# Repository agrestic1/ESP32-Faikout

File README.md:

## Support

You can support this project in many ways, including testing and diagnostics, merge requests, clearly described issues and suggestions, and [buying Faikout boards from us](https://shop.revk.uk?mrlHiG1i) (shipped worldwide). Thank you all for your support. This is open source so others can make and sell (with trademark restrictions). AI based bug reports or MRs will get you blocked.

# ESP32-Faikout

Everyone knows Daikin make some of the best air conditioners out there, mechanically speaking. Sadly their WiFi control modules are not so good, especially the latest models which are all cloud based, require an internet connection to even work, and are slow.

This code/module provides local control via web interface, MQTT, and HomeAssistant integration, all with no cloud crap.

* There is also a new [Faikout Remote Control](https://remote.revk.uk/) available, BLE linked to the Faikout, with environmental sensors, available now.

I'd like to thank the contributors, but contributions are made and accepted on basis that you issue your contribution under the same GPL licence as the project. Forks are allowed on the basis that your forks are on the same GPL licence as the project.

## Trademark

This is an open source project, but bear in mind you cannot sell boards bearing the Andrews & Arnold Ltd name, the A&A logo, the registered trademark Faikout, the registered trademark AJK logo, or the GS1 allocated EANs assigned to Andrews & Arnold Ltd.

Note the name change from Faikin to Faikout as Daikin complained to Amazon and caused a lot of issues. As such Faikout is now a registered trademark to avoid such issues.

## Home Assistant Integration

There has been a lot of work on integrating with Home Assistant as a climate device, and other sensors. This is all based on using MQTT (either HA mosquitto broker, or a broker to which HA also connects). This provides real time responses and sensor data and works very well.

In addition, for other management systems than HA, the *legacy* Daikin local HTTP URLs are also supported to some extent. The support coverage is not as good, and maintence of this is less of a priority - but as always (human) suggestions and pull requests are welcome in this area. If you are using the old Daikin HA integration which uses these legacy HTTP URLs, please update to using MQTT. The config is automatic over MQTT - you just have to set the broken, username, and password. 

## Further manuals / links

- [Work in progress](https://codeberg.org/RevK/ESP32-Faikout/wiki/Work-in-progress)
- [Wiring](https://codeberg.org/RevK/ESP32-Faikout/wiki/Wiring)
- [Setup](Manuals/Setup.md) Manual
- [Controls](Manuals/Controls.md) Manual
- [Advanced](Manuals/Advanced.md) Manual
- [ESP8266 port](https://github.com/Sonic-Amiga/ESP8266-Faikin) of this code
- [list of supported air-con](https://codeberg.org/RevK/ESP32-Faikout/wiki/List-of-confirmed-working-air-con-units) WiKi (please update as needed)
- [DoC](Manuals/DoC.md) and Vulnerability disclosure policy
- [S21](Manuals/S21.md) reverse engineered details of `S21` protocol

For support, see issues.

## Safety

Always propely isolate power before opening your air-con. Take care as dangerous voltages. Some connector types have dangerous voltage in operation.

### Ethernet (and WiFi)

The Ethernet board has an RJ45 10/100 Ethernet connector for improved reliability and privacy. The Ethernet has an isolating transformer and clearances, but I have to stress **this is a prototype/dev board for specialist/hobbyist use only, and is NOT certified for grid power safety isolation. DO NOT USE WITH X403 CONNECTOR or any connector with dangerous voltages.**

### PoE Ethernet (and WiFi)

The PoE Ethernet board has an RJ45 10/100 Ethernet connector for improved reliability and privacy, with PoE power for the Faikout module. The PoE power module has electrical isolation. The board also has opto isolators for the S21 connection, electrically isolating it from the air conditioning unit. This adds extra layers of safety, however I have to stress **this is a prototype/dev board for specialist/hobbyist use only, and is NOT certified for grid power safety isolation.**

*Note that Ethernet uses more power - there are some Daikin models with much less power from the air-con, for these PoE may be a better choice for Ethernet use, as the main board (and Ethernet chip) is powered from the PoE, and not the air-con.*

## PCB and case

Buy from [shop.revk.uk](https://shop.revk.uk?mrlHiG1i). Also available from a third party in Australia eBay.

New Ethernet option.

New Opto-isiolated PoE Ethernet option.

Board are supplied in a panel, with snap off parts. The basic Faikout board can be two sizes 45x36mm or 40x16mm.

## Why I made this

The history is that, after years of using Daikin air-con in my old home, and using the local http control, in my new house in Wales the WiFi was all cloud based with no local control, and useless, and slow. Just configuring it was a nightmare. I spent all day reverse engineering it and making a new module to provide local control. Pull requests and feature ideas welcome.

This whole project is almost entirely by me, but with some valuable contributions from others (thank you). All of my bits are copyright by me and Andrews & Arnold Ltd who sponsor the whole project, and released under GPL. Whilst not required by the licence, attribution and links would be appreciated if you reuse this.

## How to get one

But also, the PCB designs are published, including production files for [JLCPCB](https://jlcpcb.com). You need to remove trademarks, etc, and you would also need something to program them (TC2030 lead). Obviously you need some experience with PCB ordering and diagnostics if getting your own boards made.

# Set-up

Appears as access point with simple web page to set up on local WiFI. On iPhone the setup page auto-loads.

# Operation

Local interactive web control page using *hostname*.local, no app required, no external internet required.

- [Setup](Manuals/Setup.md) Manual
- [Controls](Manuals/Controls.md) Manual
- [Advanced](Manuals/Advanced.md) Manual

# Design

* KiCad PCB designs included, with JLCPCB production files
* 3D printed case STL files
* Documentation of reverse engineered protocol included

Basically, Daikin have gone all cloudy with the latest WiFi controllers. This module is designed to provide an alternative.

* Simple local web based control with live websocket status, easy to save as desktop icon on a mobile phone
* MQTT reporting and controls
* Works with Home Assistant over MQTT - note Home Assistant can work with HomeKit
* Includes linux mysql/mariadb based logging and graphing tools
* Works with [EnvMon](https://codeberg.org/RevK/ESP32-EnvMon) Environmental Monitor for finer control and status display
* or, works with BlueCoinT and Telink [BLE temperature sensor](Manuals/BLE.md) as a remote reference in an auto mode
* Automatically works out if S21 or X50 protocol (used on bigger/ducted units)
* Backwards compatible direct `/aircon/...` URLs

# Building code yourself

Git clone this `--recursive` to get all the submodules, and it should build with just `make`. There are make targets for other variations, but this hardware is the `make pico` or `make s3` version. The `make` actually runs the normal `idf.py` to build which then uses cmake. `make menuconfig` can be used to fine tune the settings, but the defaults should be mostly sane. `make flash` should work to program. If flashing yourself, you will need a programming lead, e.g. [Tazmotizer](https://codeberg.org/RevK/Tasmotizer-PCB) or similar, and of course the full ESP IDF environment. The latest boards also have 4 pads for direct USB connection to flash with no adaptor. The modules on Amazon come pre-loaded and can upgrade over the air.

The code is normally set up to automatically upgrade the software, checking roughly once a week. You can change this in settings via MQTT.

If you build yourself, you either need no code signing, or your own signing key. This will break auto-updates which try to load my code releases, so you need to adjuist settings `otahost` and `otaauto` accordingly. You can set these in the build config, along with WiFi settings, etc.

## Flashing code

You will need to connect a suitable programming lead. Boards have a tag-connect compatible header for a [TC2030-USB-NL](https://www.tag-connect.com/product/tc2030-usb-nl) lead. Note that the latest boards have test pads on the back which include USB, so you can solder a USB lead if necessary.

See [https://codeberg.org/RevK/ESP32-RevK](https://codeberg.org/RevK/ESP32-RevK) for more details of how to flash the files easily.

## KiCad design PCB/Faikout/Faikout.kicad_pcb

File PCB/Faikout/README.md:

# Faikout

## Trademark

This project is subject to the licence in the LICENCE file, and even if that says it is an open source project, you cannot sell boards or cases bearing the Andrews & Arnold Ltd name, the A&A logo, the registered trademark AJK logo, or other registered trademarks, or any GS1 allocated EANs/barcode assigned to Andrews & Arnold Ltd.

## PCB Designs

These files are for use with [KiCAD](https://www.kicad.org).

- [Faikout](Faikout.kicad_pro)

## 3D

3D case designs are normally automatically created from the PCB so as to ensure correct details and placement of apertures, etc.

|Design|Bottom|Top|Combined|
|------|------|---|--------|
|Faikout||||

## PCB Images Faikout

---

*Auto generated README.md 2026-11-19T10:28:16*

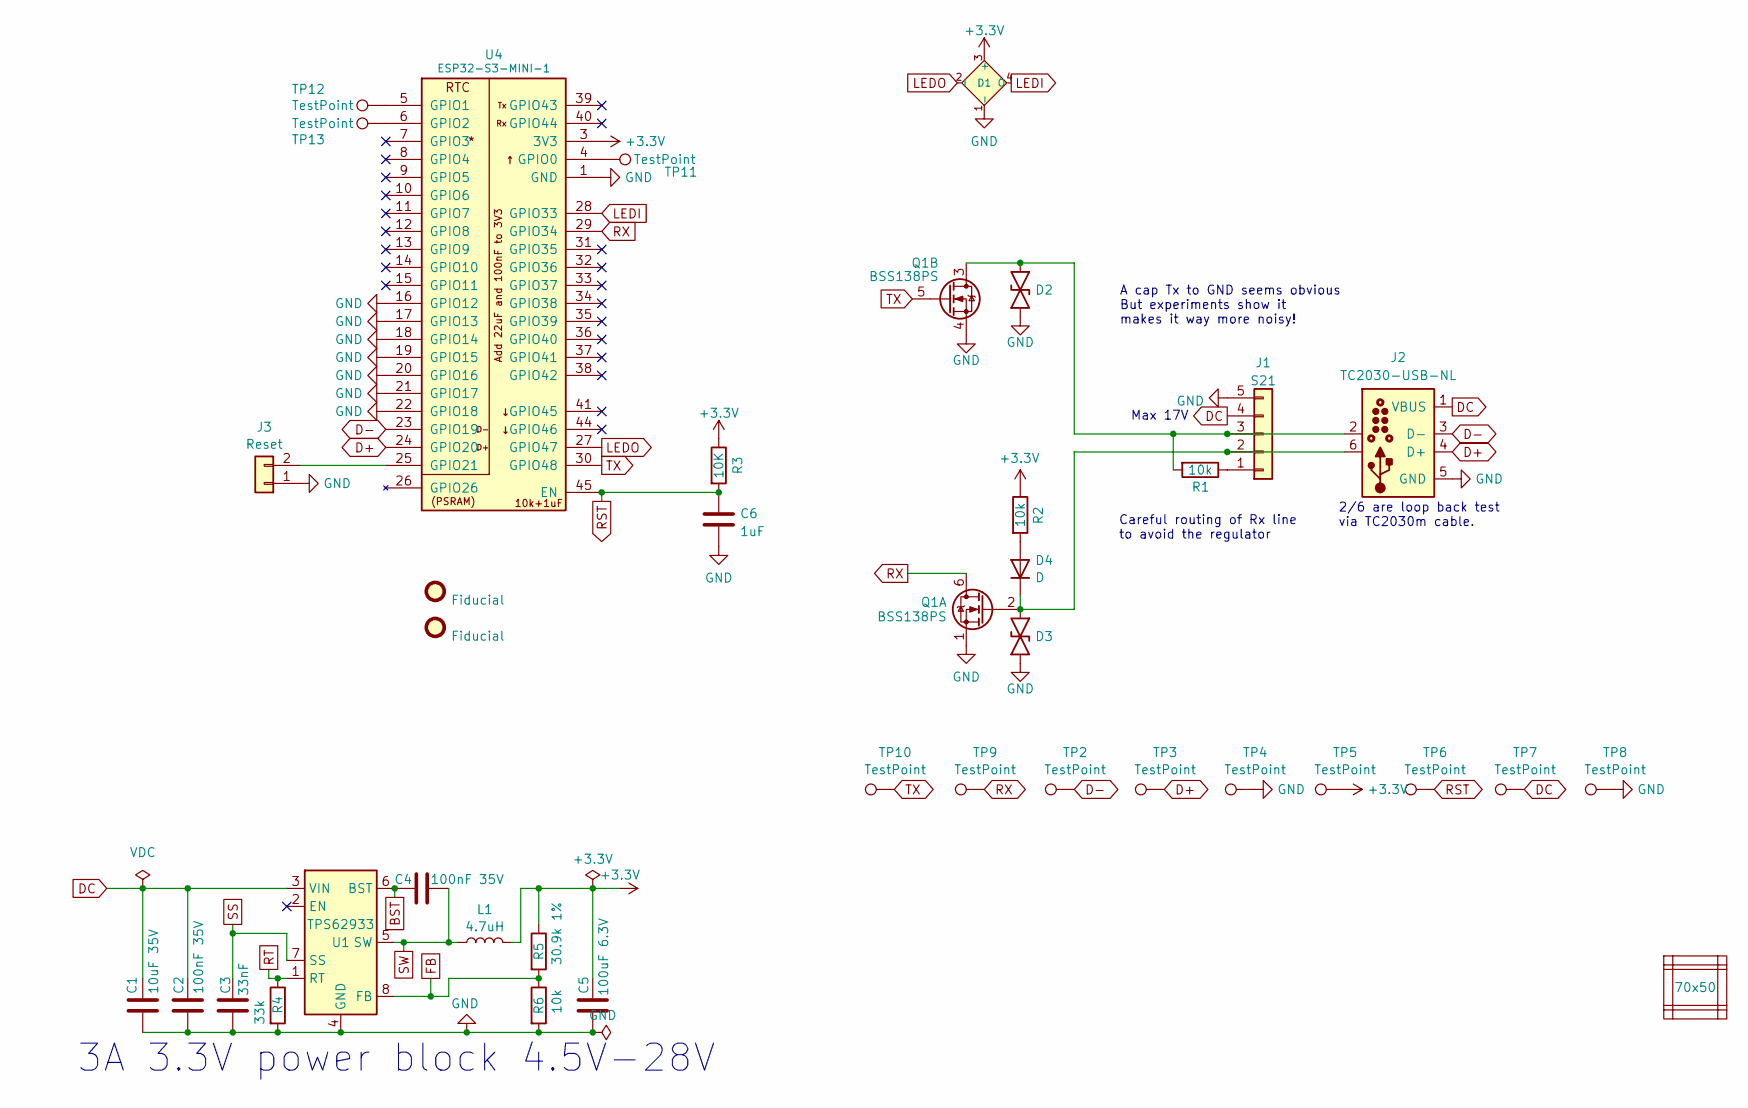
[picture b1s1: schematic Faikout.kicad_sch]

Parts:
C1: 10uF 35V; C_0603; MPN C22367827
C2, C4: 100nF 35V; C_0201; MPN C181043
C3: 33nF; C_0201; MPN C5142554
C5: 100uF 6.3V; C_0805; MPN C141660
C6: 1uF; C_0201
D1: XL-1615RGBC-2812B; SMD1615; MPN C5349954
D2, D3: DFN1006-2L; MPN C5137770
D4: D; D_0402; MPN C28642302
FID2, FID3: Fiducial; Fiducial_1mm_Mask2mm
J1: S21; JST_EH_S5B-EH_1x05_P2.50mm_Horizontal; MPN C265103
J2: TC2030-USB-NL; Tag-Connect_TC2030-IDC-NL_2x03_P1.27mm_Vertical
J3: Reset; AA-Pad
L1: 4.7uH; L_6x6; MPN C32684
PCB1: 70x50; PCB7050
Q1: BSS138PS; SOT-363_SC-70-6; MPN C5224289
R1, R2, R6: 10k; R_0201; MPN C106225
R3: 10K; R_0201; MPN C106225
R4: 33k; R_0201; MPN C473534
R5: 30.9k 1%; R_0201; MPN C473585
TP2, TP3, TP4, TP5, TP6, TP7, TP8, TP9, TP10, TP11, TP12, TP13: TestPoint; PAD-2mm
U1: TPS62933; SOT-583-8; MPN C3200405
U4: ESP32-S3-MINI-1; MPN C3013941
V1, V2, V3, V4: VCUT70N
V5, V6: VCUT50N

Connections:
+3.3V: C5.1, D1.3 (+), L1.2, R2.1, R3.1, R5.1, TP5.1 (1_1), U4.3 (3V3)
BST: C4.1, U1.6 (BST)
D+: J2.4 (D+), TP3.1 (1_1), U4.24 (GPIO20)
D-: J2.3 (D-), TP2.1 (1_1), U4.23 (GPIO19)
DC: C1.1, C2.1, J1.4, J2.1 (VBUS), TP7.1 (1_1), U1.3 (VIN)
FB: R5.2, R6.1, U1.8 (FB)
GND: C1.2, C2.2, C3.2, C5.2, C6.2, D1.1 (-), D2.1, D3.1, J1.5, J2.5 (GND), J3.1, Q1.1 (SN), Q1.4 (DP), R4.2, R6.2, TP4.1 (1_1), TP8.1 (1_1), U1.4 (GND), U4.1 (GND), U4.2 (GND), U4.16 (GPIO12), U4.17 (GPIO13), U4.18 (GPIO14), U4.19 (GPIO15), U4.20 (GPIO16), U4.21 (GPIO17), U4.22 (GPIO18), U4.42 (GND), U4.43 (GND), U4.46 (GND), U4.47 (GND), U4.48 (GND), U4.49 (GND), U4.50 (GND), U4.51 (GND), U4.52 (GND), U4.53 (GND), U4.54 (GND), U4.55 (GND), U4.56 (GND), U4.57 (GND), U4.58 (GND), U4.59 (GND), U4.60 (GND), U4.61 (GND), U4.62 (GND), U4.63 (GND), U4.64 (GND), U4.65 (GND)
LEDI: D1.4 (O), U4.28 (GPIO33)
LEDO: D1.2 (I), U4.27 (GPIO47)
unnamed: D4.2 (A), R2.2
unnamed: D3.2, D4.1 (K), J1.2, J2.6, Q1.2 (GN)
unnamed: J1.1, R1.1
unnamed: D2.2, J1.3, J2.2, Q1.3 (SP), R1.2
unnamed: J3.2, U4.25 (GPIO21)
unnamed: TP11.1 (1_1), U4.4 (GPIO0)
unnamed: TP12.1 (1_1), U4.5 (GPIO1)
unnamed: TP13.1 (1_1), U4.6 (GPIO2)
RST: C6.1, R3.2, TP6.1 (1_1), U4.45 (EN)
RT: R4.1, U1.1 (RT)
RX: Q1.6 (DN), TP9.1 (1_1), U4.29 (GPIO34)
SS: C3.1, U1.7 (SS)
SW: C4.2, L1.1, U1.5 (SW)
TX: Q1.5 (GP), TP10.1 (1_1), U4.30 (GPIO48)

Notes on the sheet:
Careful routing of Rx line to avoid the regulator
3A 3.3V power block 4.5V-28V
Max 17V
2/6 are loop back test via TC2030m cable.
A cap Tx to GND seems obvious But experiments show it makes it way more noisy!

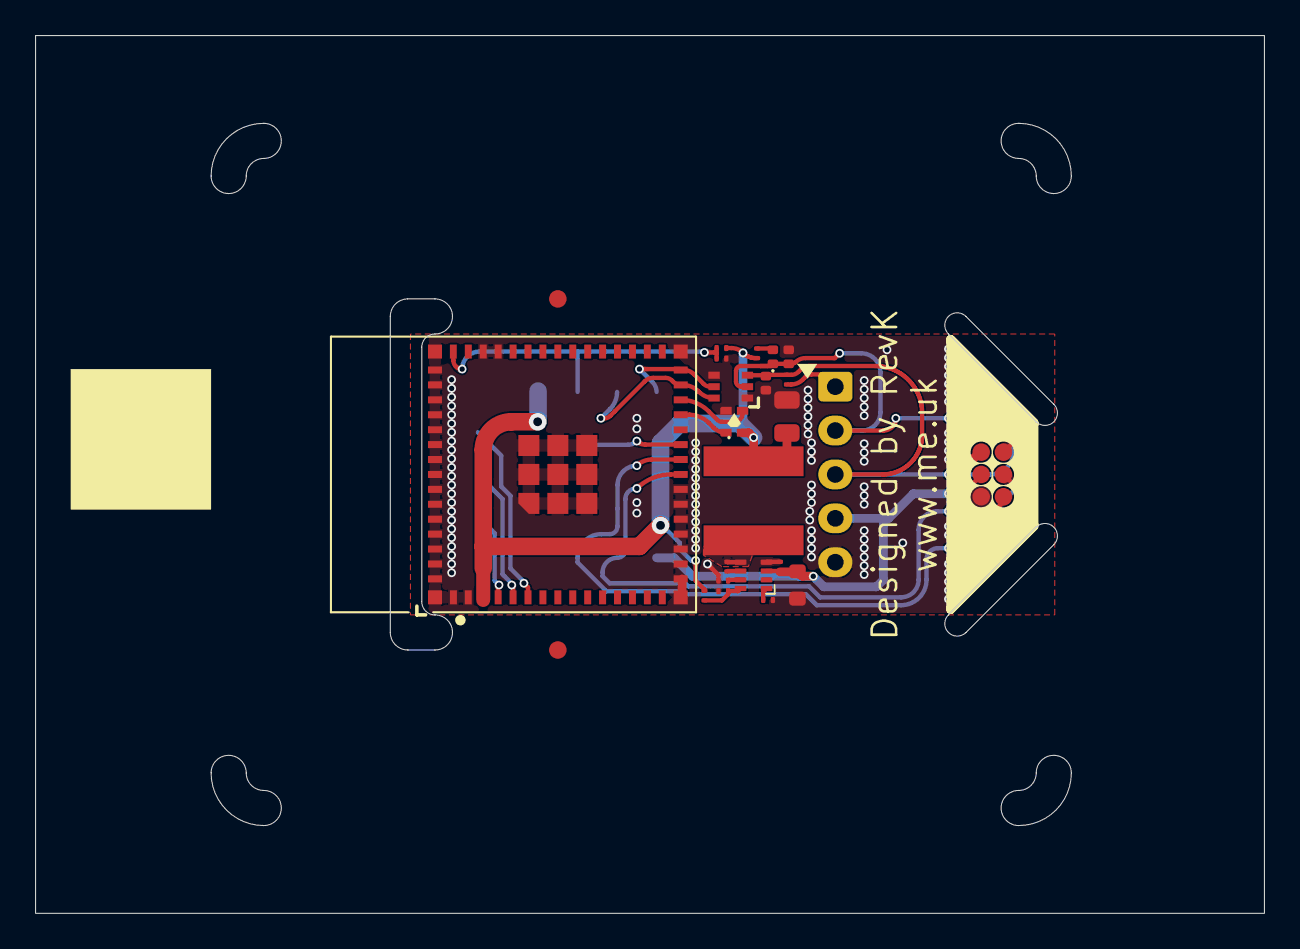
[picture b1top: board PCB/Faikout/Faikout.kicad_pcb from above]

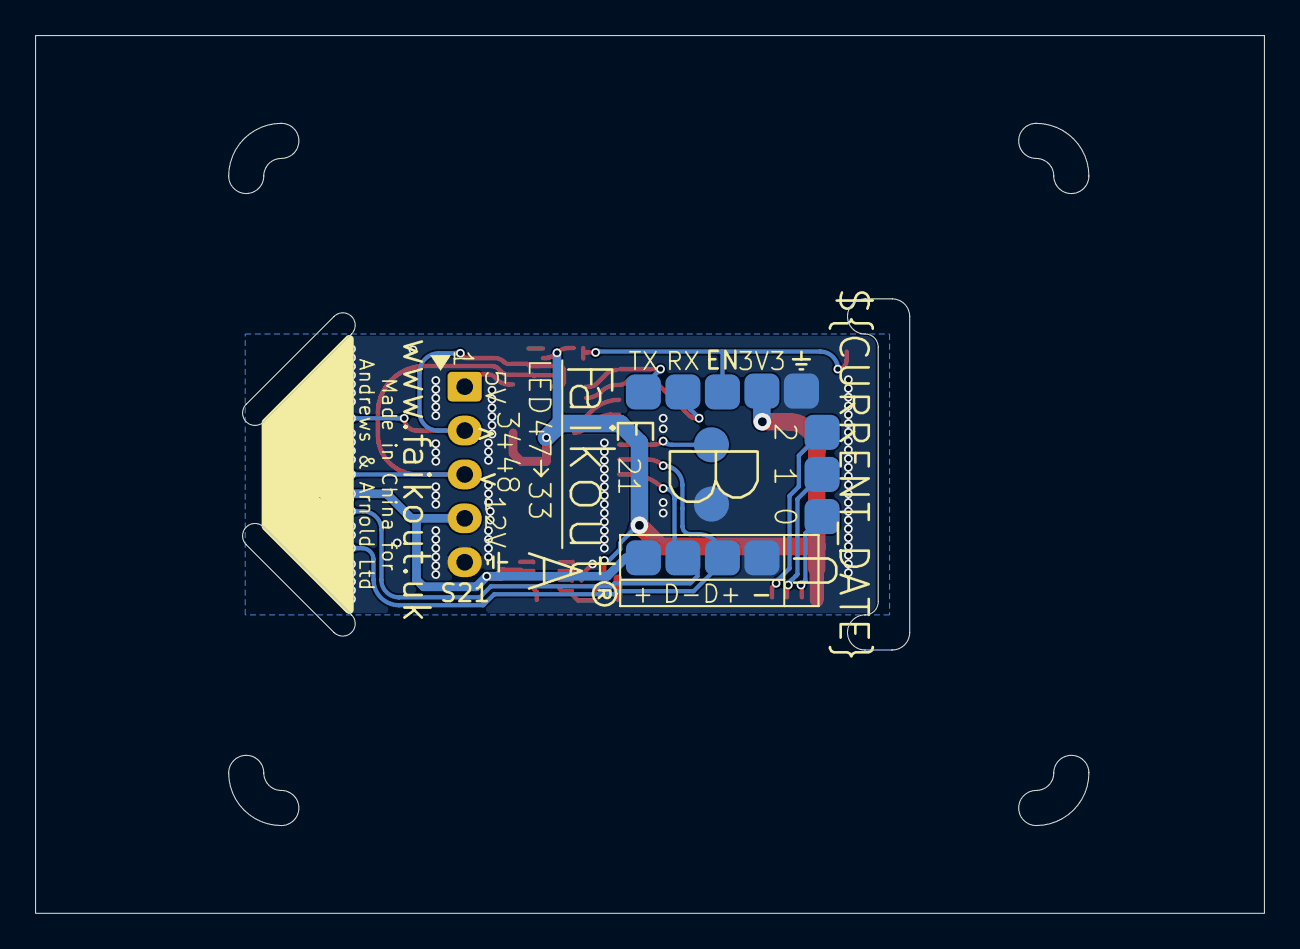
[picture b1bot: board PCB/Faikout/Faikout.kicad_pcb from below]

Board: 2 copper layers, 70.0 x 50.0 mm, 44 parts (15 on the bottom side), 23 nets.

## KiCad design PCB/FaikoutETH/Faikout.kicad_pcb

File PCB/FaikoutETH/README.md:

# FaikoutETH

## Trademark

This project is subject to the licence in the LICENCE file, and even if that says it is an open source project, you cannot sell boards or cases bearing the Andrews & Arnold Ltd name, the A&A logo, the registered trademark AJK logo, or other registered trademarks, or any GS1 allocated EANs/barcode assigned to Andrews & Arnold Ltd.

## PCB Designs

These files are for use with [KiCAD](https://www.kicad.org).

- [Faikout](Faikout.kicad_pro)

## 3D

3D case designs are normally automatically created from the PCB so as to ensure correct details and placement of apertures, etc.

|Design|Bottom|Top|Combined|
|------|------|---|--------|
|Faikout||||

## PCB Images Faikout

---

*Auto generated README.md 2026-11-19T10:28:18*

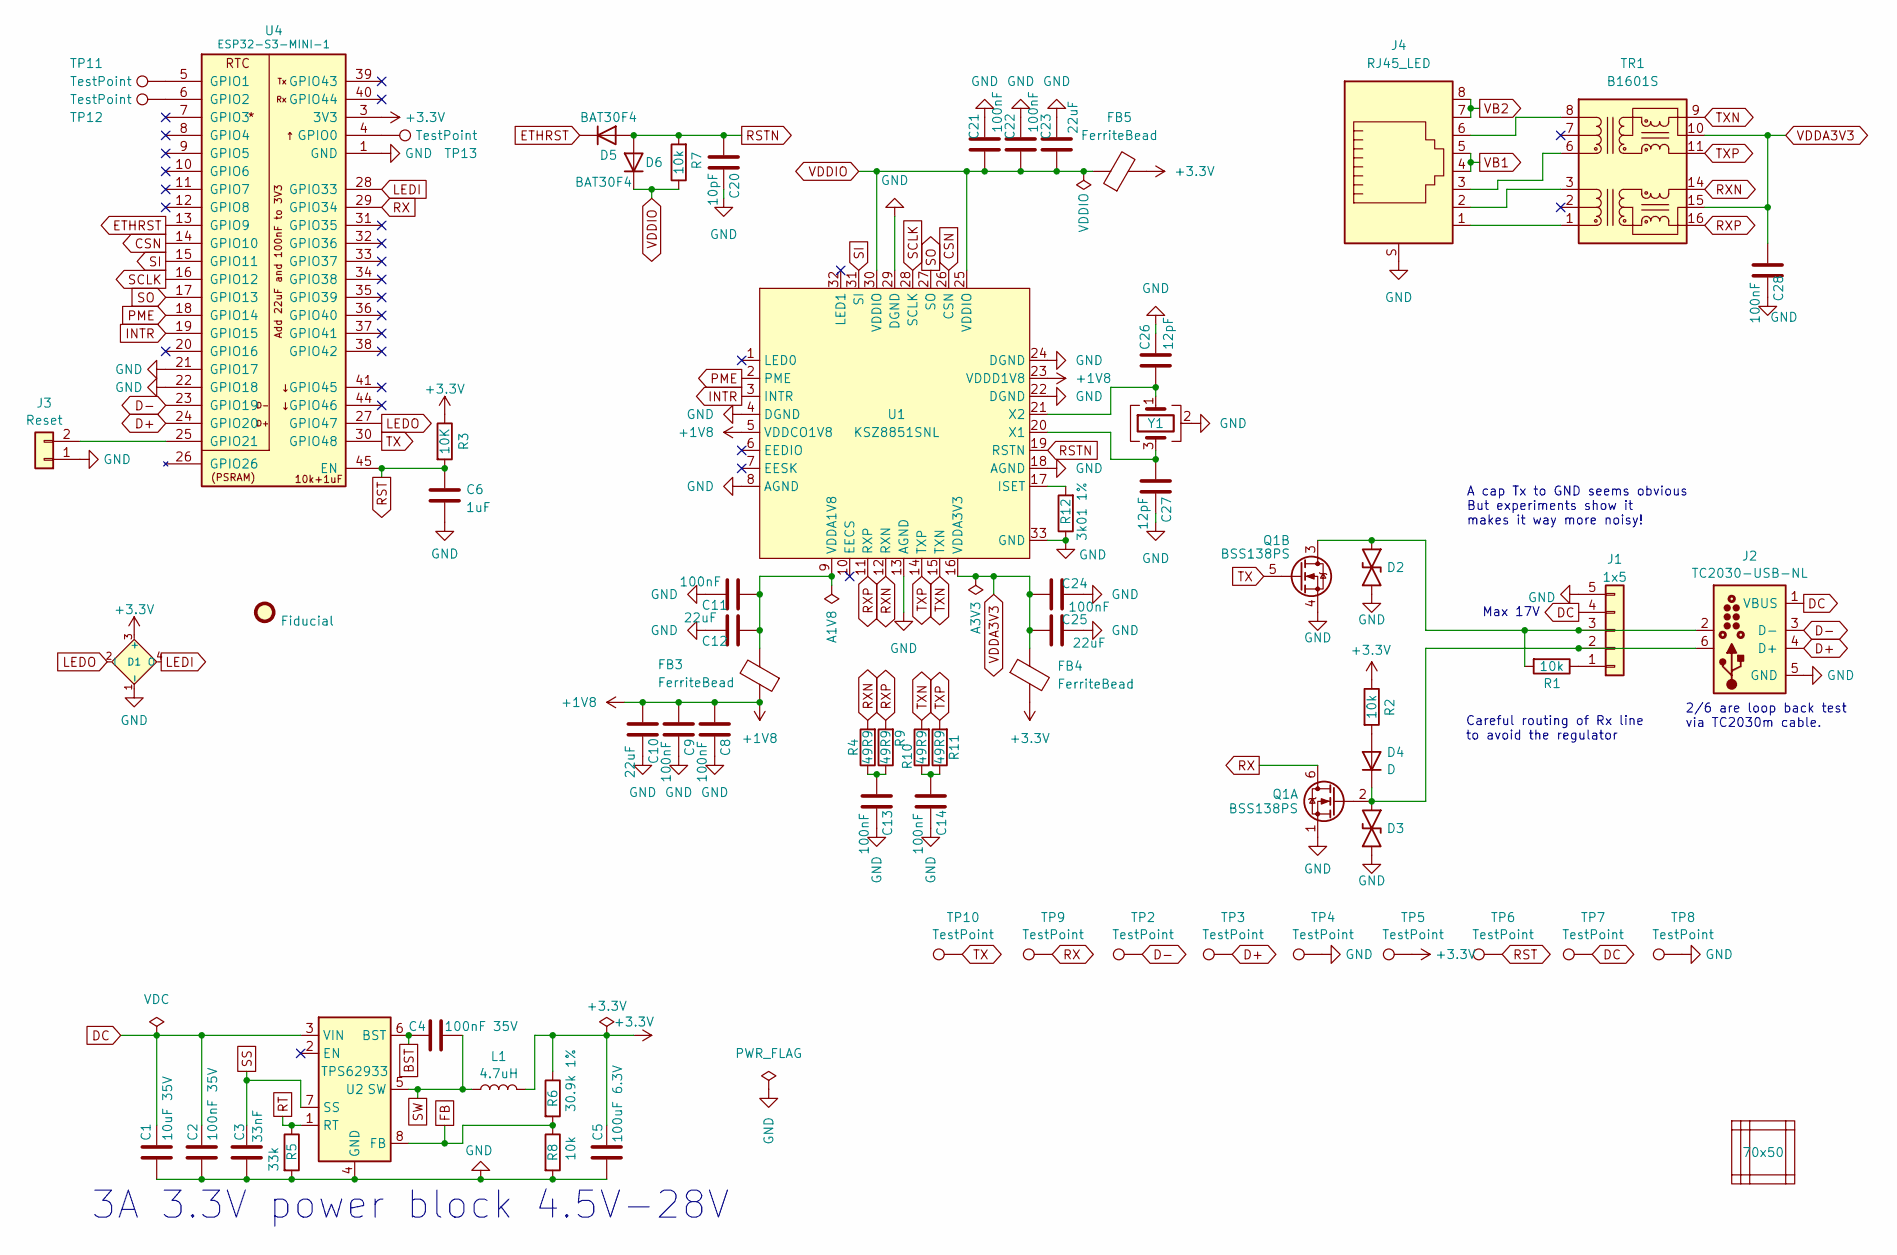
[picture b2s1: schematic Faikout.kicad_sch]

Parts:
C1: 10uF 35V; C_0603; MPN C22367827
C2, C4: 100nF 35V; C_0201; MPN C181043
C3: 33nF; C_0201; MPN C5142554
C5: 100uF 6.3V; C_0805; MPN C141660
C6: 1uF; C_0201; MPN C87143
C8, C9, C11, C13, C14, C21, C22, C24, C28: 100nF; C_0201; MPN C66938
C10, C12, C23, C25: 22uF; C_0402; MPN C105226
C20: 10pF; C_0201; MPN C76921
C26, C27: 12pF; C_0201
D1: XL-1615RGBC-2812B; SMD1615; MPN C5349954
D2, D3: DFN1006-2L; MPN C5137770
D4: D; D_0402; MPN C28642302
D5, D6: BAT30F4; D_0201; MPN C18197832
FB3, FB4, FB5: FerriteBead; L_0603; MPN C14709
FID2: Fiducial; Fiducial_1mm_Mask2mm
J1: 1x5; JST_EH_S5B-EH_1x05_P2.50mm_Horizontal; MPN C265103
J2: TC2030-USB-NL; Tag-Connect_TC2030-IDC-NL_2x03_P1.27mm_Vertical
J3: Reset; AA-Pad
J4: RJ45_LED; RC01516; MPN C708636
L1: 4.7uH; L_6x6; MPN C32684
PCB1: 70x50; PCB7050
Q1: BSS138PS; SOT-363_SC-70-6; MPN C193381
R1, R2, R7: 10k; R_0201; MPN C138117
R3: 10K; R_0201; MPN C138117
R4, R9, R10, R11: 49R9; R_0201; MPN C100141
R5: 33k; R_0201; MPN C473534
R6: 30.9k 1%; R_0201; MPN C473585
R8: 10k; R_0201; MPN C106225
R12: 3k01 1%; R_0201; MPN C320817
TP2, TP3, TP4, TP5, TP6, TP7, TP8, TP9, TP10, TP11, TP12, TP13: TestPoint; PAD-2mm
TR1: B1601S; MPN C510548
U1: KSZ8851SNL; QFN-32-1EP_5x5mm_P0.5mm_EP3.7x3.7mm-hot; MPN C633272
U2: TPS62933; SOT-583-8; MPN C3200405
U4: ESP32-S3-MINI-1; MPN C3013941
V3, V4: VCUT70N
V5, V6, V7: VCUT50N
Y1: Crystal_GND24; Crystal-3.2x2.5; MPN C5155480

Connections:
+1V8: C8.1, C9.1, C10.1, FB3.1, U1.5 (VDDCO1V8), U1.23 (VDDD1V8)
+3.3V: C5.1, D1.3 (+), FB4.2, FB5.2, L1.2, R2.1, R3.1, R6.1, TP5.1 (1_1), U4.3 (3V3)
BST: C4.1, U2.6 (BST)
CSN: U1.26 (CSN), U4.14 (GPIO10)
D+: J2.4 (D+), TP3.1 (1_1), U4.24 (GPIO20)
D-: J2.3 (D-), TP2.1 (1_1), U4.23 (GPIO19)
DC: C1.1, C2.1, J1.4, J2.1 (VBUS), TP7.1 (1_1), U2.3 (VIN)
ETHRST: D5.1 (K), U4.13 (GPIO9)
FB: R6.2, R8.1, U2.8 (FB)
GND: C1.2, C2.2, C3.2, C5.2, C6.2, C8.2, C9.2, C10.2, C11.2, C12.2, C13.2, C14.2, C20.2, C21.2, C22.2, C23.2, C24.2, C25.2, C26.2, C27.2, C28.2, D1.1 (-), D2.1, D3.1, J1.5, J2.5 (GND), J3.1, J4.S, Q1.1 (SN), Q1.4 (DP), R5.2, R8.2, R12.1, TP4.1 (1_1), TP8.1 (1_1), U1.4 (DGND), U1.8 (AGND), U1.13 (AGND), U1.18 (AGND), U1.22 (DGND), U1.24 (DGND), U1.29 (DGND), U1.33 (GND), U2.4 (GND), U4.1 (GND), U4.2 (GND), U4.21 (GPIO17), U4.22 (GPIO18), U4.42 (GND), U4.43 (GND), U4.46 (GND), U4.47 (GND), U4.48 (GND), U4.49 (GND), U4.50 (GND), U4.51 (GND), U4.52 (GND), U4.53 (GND), U4.54 (GND), U4.55 (GND), U4.56 (GND), U4.57 (GND), U4.58 (GND), U4.59 (GND), U4.60 (GND), U4.61 (GND), U4.62 (GND), U4.63 (GND), U4.64 (GND), U4.65 (GND), Y1.2 (G), Y1.4 (G)
INTR: U1.3 (INTR), U4.19 (GPIO15)
LEDI: D1.4 (O), U4.28 (GPIO33)
LEDO: D1.2 (I), U4.27 (GPIO47)
unnamed: C13.1, R4.1, R9.1
unnamed: C14.1, R10.1, R11.1
unnamed: D4.2 (A), R2.2
unnamed: D3.2, D4.1 (K), J1.2, J2.6, Q1.2 (GN)
unnamed: J1.1, R1.1
unnamed: D2.2, J1.3, J2.2, Q1.3 (SP), R1.2
unnamed: J3.2, U4.25 (GPIO21)
unnamed: J4.3, TR1.6 (RD+)
unnamed: J4.6, TR1.8 (RD-)
unnamed: J4.1, TR1.1 (TD+)
unnamed: J4.2, TR1.3 (TD-)
unnamed: R12.2, U1.17 (ISET)
unnamed: C11.1, C12.1, FB3.2, U1.9 (VDDA1V8)
unnamed: C27.1, U1.20 (X1), Y1.3
unnamed: C26.1, U1.21 (X2), Y1.1
unnamed: TP13.1 (1_1), U4.4 (GPIO0)
unnamed: TP11.1 (1_1), U4.5 (GPIO1)
unnamed: TP12.1 (1_1), U4.6 (GPIO2)
PME: U1.2 (PME), U4.18 (GPIO14)
RST: C6.1, R3.2, TP6.1 (1_1), U4.45 (EN)
RSTN: C20.1, D5.2 (A), D6.2 (A), R7.2, U1.19 (RSTN)
RT: R5.1, U2.1 (RT)
RX: Q1.6 (DN), TP9.1 (1_1), U4.29 (GPIO34)
RXN: R4.2, TR1.14 (TX-), U1.12 (RXN)
RXP: R9.2, TR1.16 (TX+), U1.11 (RXP)
SCLK: U1.28 (SCLK), U4.16 (GPIO12)
SI: U1.31 (SI), U4.15 (GPIO11)
SO: U1.27 (SO), U4.17 (GPIO13)
SS: C3.1, U2.7 (SS)
SW: C4.2, L1.1, U2.5 (SW)
TX: Q1.5 (GP), TP10.1 (1_1), U4.30 (GPIO48)
TXN: R10.2, TR1.9 (RX-), U1.15 (TXN)
TXP: R11.2, TR1.11 (RX+), U1.14 (TXP)
VB1: J4.4, J4.5
VB2: J4.7, J4.8
VDDA3V3: C24.1, C25.1, C28.1, FB4.1, TR1.10 (C_RX), TR1.15 (C_TX), U1.16 (VDDA3V3)
VDDIO: C21.1, C22.1, C23.1, D6.1 (K), FB5.1, R7.1, U1.25 (VDDIO), U1.30 (VDDIO)

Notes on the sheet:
Careful routing of Rx line to avoid the regulator
Max 17V
2/6 are loop back test via TC2030m cable.
A cap Tx to GND seems obvious But experiments show it makes it way more noisy!
3A 3.3V power block 4.5V-28V

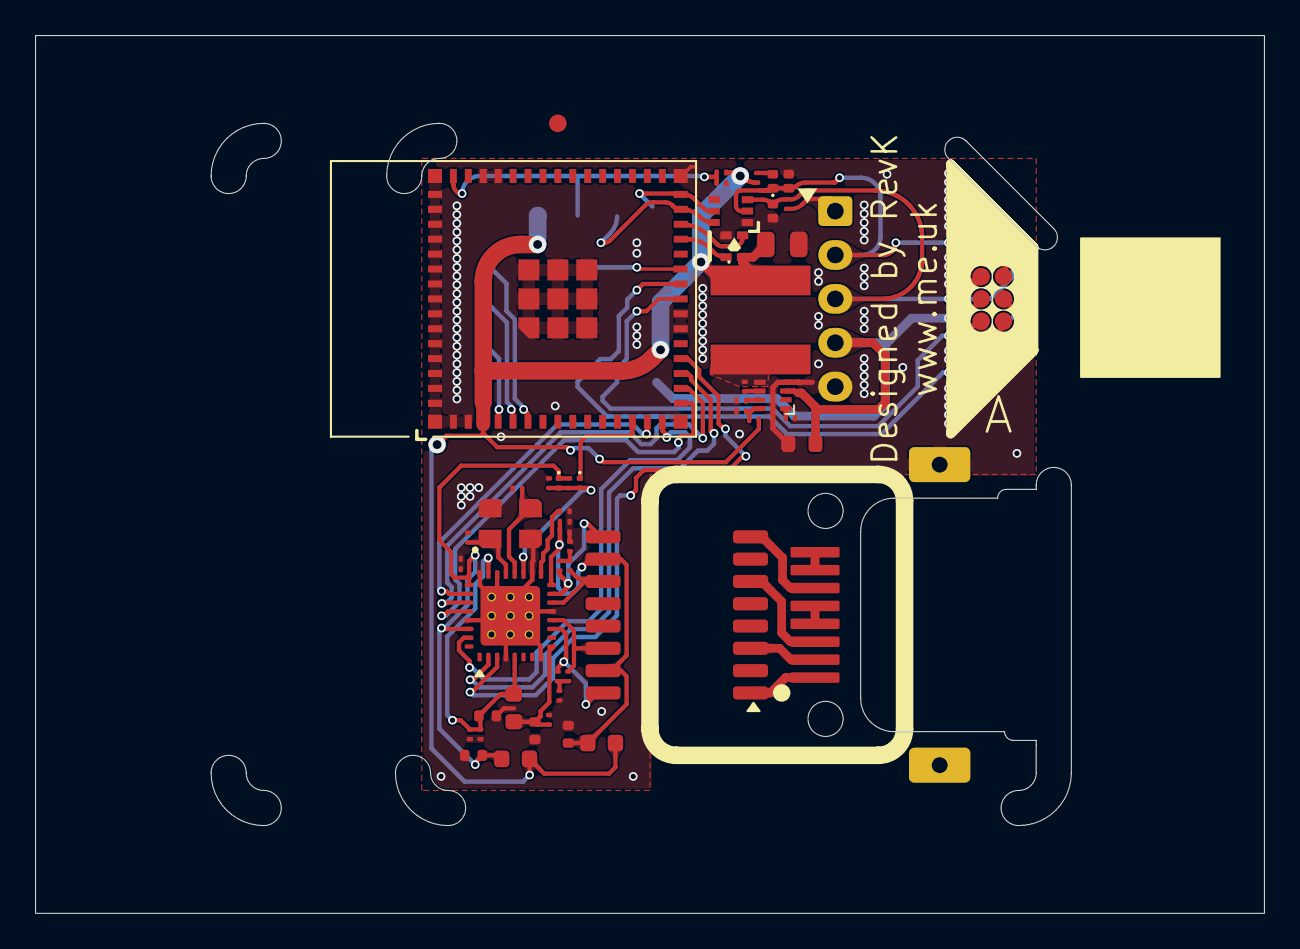
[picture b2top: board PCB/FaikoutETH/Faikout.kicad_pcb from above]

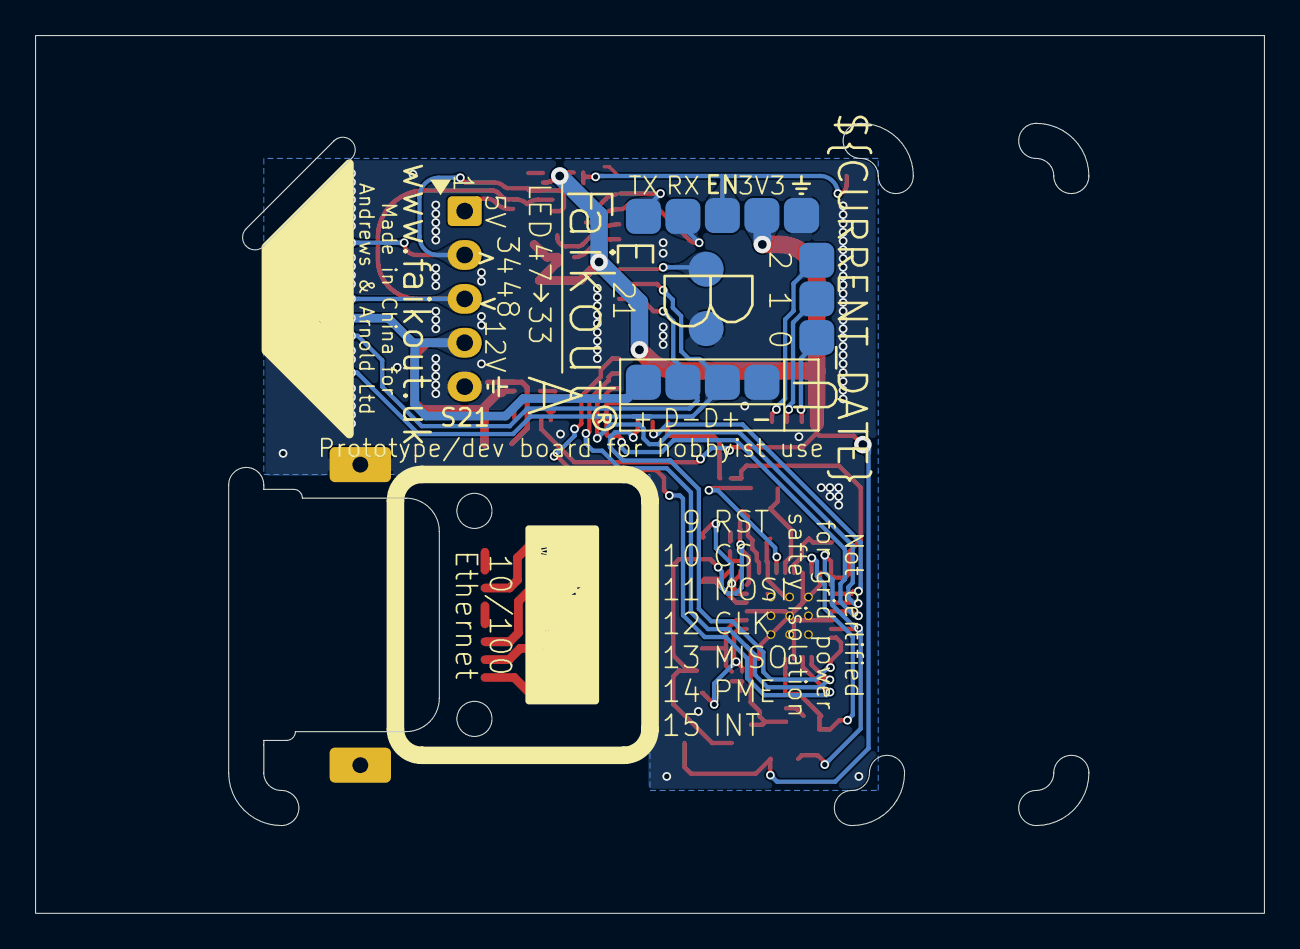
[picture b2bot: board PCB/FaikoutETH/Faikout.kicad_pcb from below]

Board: 2 copper layers, 70.0 x 50.0 mm, 73 parts (14 on the bottom side), 50 nets.

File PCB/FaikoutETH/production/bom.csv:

Designator,Footprint,Quantity,Value,LCSC Part #
C1,C_0603,1,10uF 35V,C22367827
"C10, C12, C23, C25",C_0402,4,22uF,C105226
"C11, C13, C14, C21, C22, C24, C28, C8, C9",C_0201,9,100nF,C66938
"C2, C4",C_0201,2,100nF 35V,C181043
C20,C_0201,1,10pF,C76921
"C26, C27",C_0201,2,12pF,
C3,C_0201,1,33nF,C5142554
C5,C_0805,1,100uF 6.3V,C141660
C6,C_0201,1,1uF,C87143
D1,SMD1615,1,XL-1615RGBC-2812B,C5349954
"D2, D3",DFN1006-2L,2,~,C5137770
D4,D_0402,1,D,C28642302
"D5, D6",D_0201,2,BAT30F4,C18197832
"FB3, FB4, FB5",L_0603,3,FerriteBead,C14709
J1,JST_EH_S5B-EH_1x05_P2.50mm_Horizontal,1,1x5,C265103
J4,RC01516,1,RJ45_LED,C708636
L1,L_6x6,1,4.7uH,C32684
Q1,SOT-363_SC-70-6,1,BSS138PS,C193381
"R1, R2, R3, R7",R_0201,4,10k,C138117
"R10, R11, R4, R9",R_0201,4,49R9,C100141
R12,R_0201,1,3k01 1%,C320817
R5,R_0201,1,33k,C473534
R6,R_0201,1,30.9k 1%,C473585
R8,R_0201,1,10k,C106225
TR1,B1601S,1,B1601S,C510548
U1,QFN-32-1EP_5x5mm_P0.5mm_EP3.7x3.7mm-hot,1,KSZ8851SNL,C633272
U2,SOT-583-8,1,TPS62933,C3200405
U4,ESP32-S3-MINI-1,1,ESP32-S3-MINI-1,C3013941
Y1,Crystal-3.2x2.5,1,Crystal_GND24,C5155480
